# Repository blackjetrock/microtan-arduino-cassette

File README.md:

# microtan-arduino-cassette
Arduino based cassette system for Microtan computer

Uses Arduino Mega or Uno, depending on how much memory you need. Uno has 2K RAM mega has 8K. You can't use all of it for a buffer to store cassette information.

The connections to the cassette interface are not the external ones that attach to a tape recorder. They are instead pins 11 and 12 of connector B1 on the TANEX. This is logic level and removes the need for amplifiers and so on. Ground is also needed on B1.

The code runs only in fast mode. The data read from the Microtan is dumped to a buffer that can then go to an SD card.

SD card read isn't working yet.

When using the SAVE command the code displays data as it is received. The serial port on the Arduino runs at 115200 and there's enough time to send the bytes out of the port as the data is received.

Commands

clear:    Clears the memory buffer ready for a new SAVE.

display:  Displays the current contents of the buffer

savefile: Saves the buffer to a file on the attached SD card. The filename used is the embedded name in the data. 
          Data is curently saved in ASCII hex but binary is probably better as it can be directly sent back to the Microtan.

send:     Sends the data buffer back to the Microtan. There's a spurious byte at the start of the buffer that isn't sent back.

There are other commands used in development, I need to remove those or at least tidy them up.

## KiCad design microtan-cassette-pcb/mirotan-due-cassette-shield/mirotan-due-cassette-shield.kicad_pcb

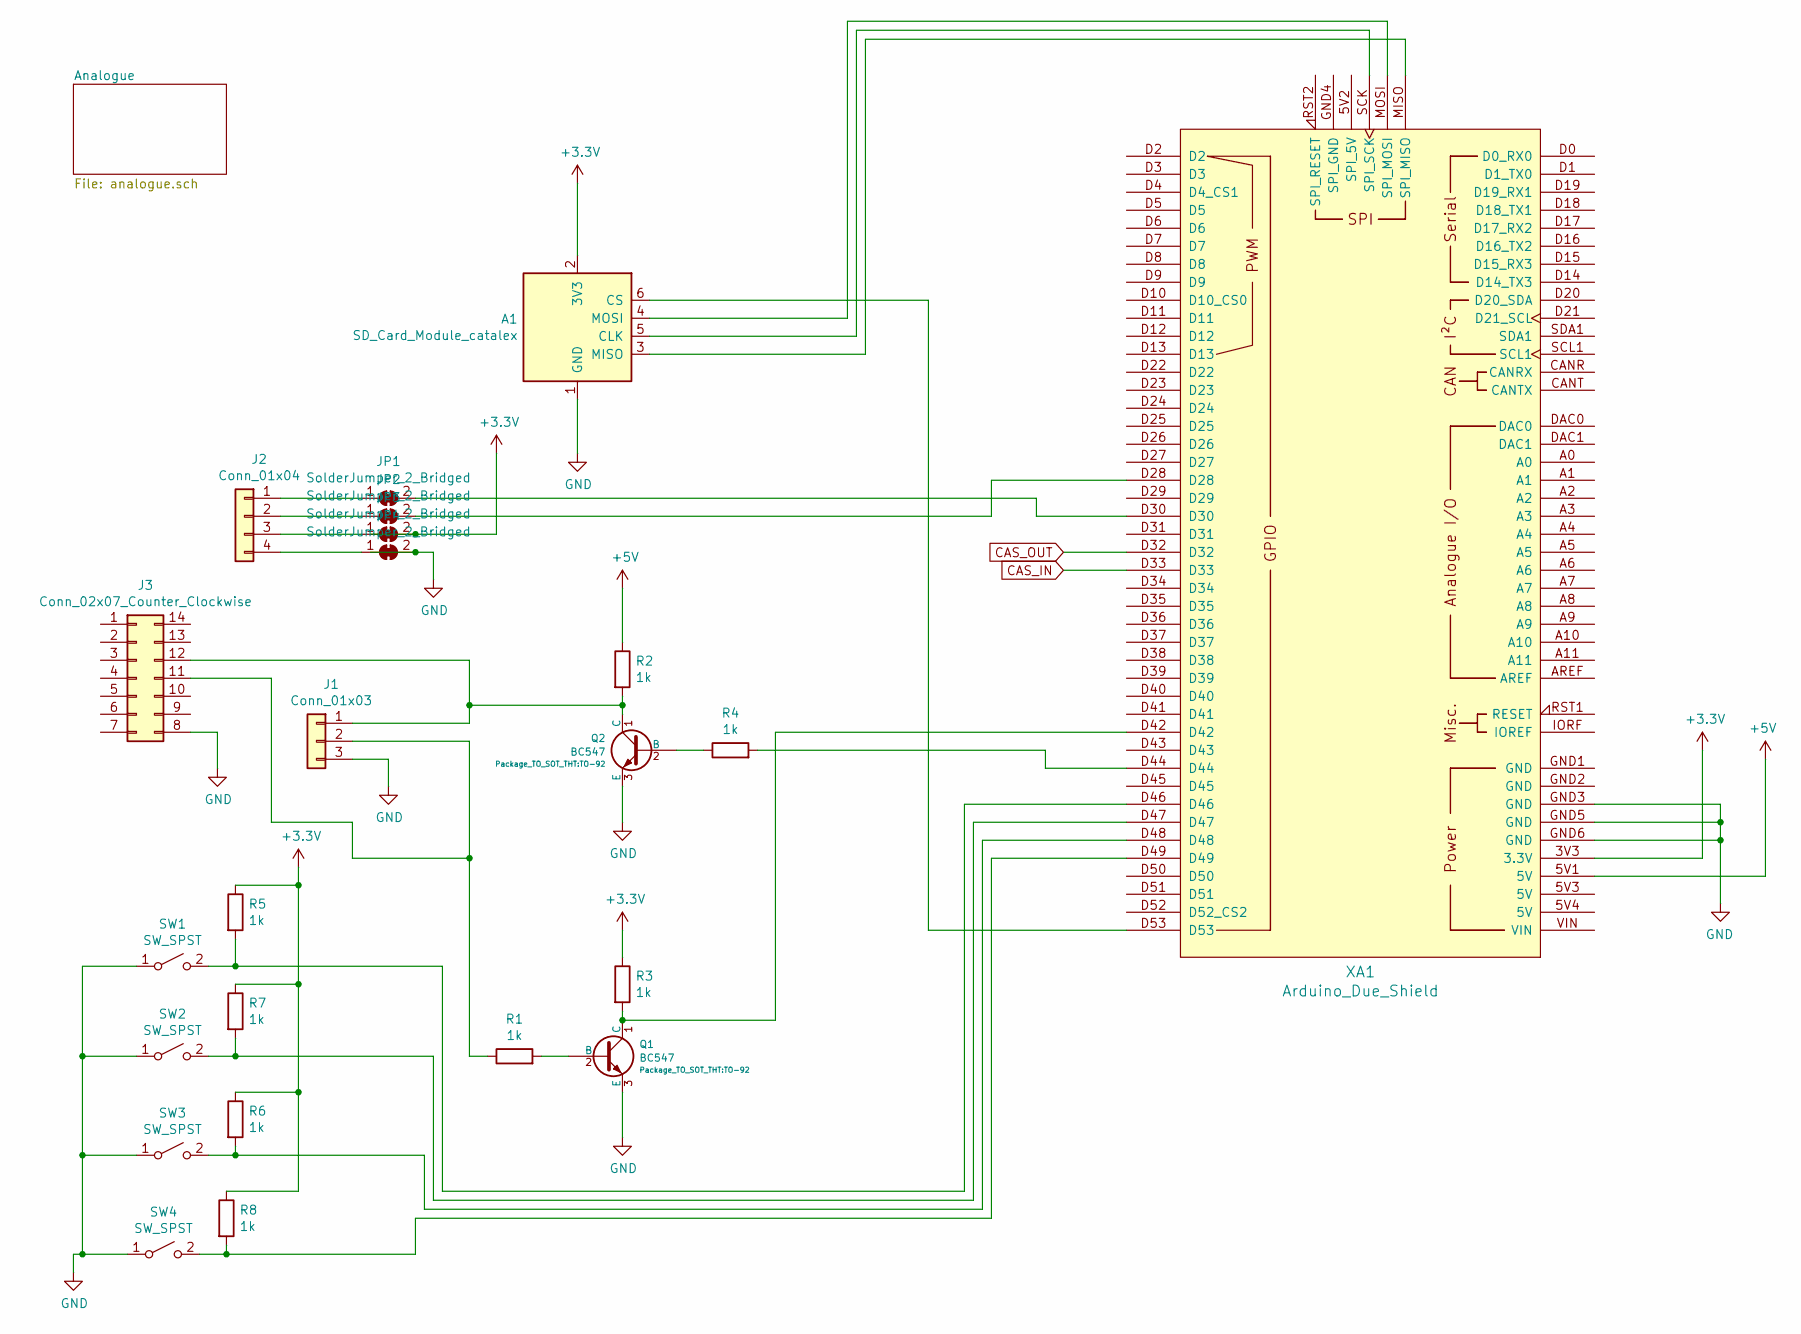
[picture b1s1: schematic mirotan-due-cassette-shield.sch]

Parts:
A1: SD_Card_Module_catalex; SD_Card_Module
J1: Conn_01x03; Molex_KK-254_AE-6410-03A_1x03_P2.54mm_Vertical
J2: Conn_01x04; Molex_KK-254_AE-6410-04A_1x04_P2.54mm_Vertical
J3: Conn_02x07_Counter_Clockwise; DIP-14_W7.62mm_Socket
JP1, JP2, JP3, JP4: SolderJumper_2_Bridged; SolderJumper-2_P1.3mm_Bridged2Bar_RoundedPad1.0x1.5mm
Q1, Q2: BC547; TO-92
R1, R2, R3, R4, R5, R6, R7, R8: 1k; R_Axial_DIN0207_L6.3mm_D2.5mm_P7.62mm_Horizontal
SW1, SW2, SW3, SW4: SW_SPST; SW_PUSH-12mm
XA1: Arduino_Due_Shield

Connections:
+3V3: A1.2 (3V3), JP3.2 (B), R3.1, R5.1, R6.1, R7.1, R8.1, XA1.3V3 (3.3V)
+5V: R2.1, XA1.5V1 (5V); also elsewhere on the board
CAS_IN: XA1.D33; also elsewhere on the board
CAS_OUT: XA1.D32; also elsewhere on the board
GND: A1.1 (GND), J1.3, J3.8, JP4.2 (B), Q1.3 (E), Q2.3 (E), SW1.1 (A), SW2.1 (A), SW3.1 (A), SW4.1 (A), XA1.GND3 (GND), XA1.GND5 (GND), XA1.GND6 (GND); also elsewhere on the board
unnamed: A1.3 (MISO), XA1.MISO (SPI_MISO)
unnamed: A1.4 (MOSI), XA1.MOSI (SPI_MOSI)
unnamed: A1.5 (CLK), XA1.SCK (SPI_SCK)
unnamed: A1.6 (CS), XA1.D53
unnamed: J1.1, J3.12, Q2.1 (C), R2.2
unnamed: J1.2, J3.11, R1.1
unnamed: J2.1, JP1.1 (A)
unnamed: J2.2, JP2.1 (A)
unnamed: J2.3, JP3.1 (A)
unnamed: J2.4, JP4.1 (A)
unnamed: JP1.2 (B), XA1.D30
unnamed: JP2.2 (B), XA1.D28
unnamed: Q1.1 (C), R3.2, XA1.D42
unnamed: Q1.2 (B), R1.2
unnamed: Q2.2 (B), R4.1
unnamed: R4.2, XA1.D44
unnamed: R5.2, SW1.2 (B), XA1.D46
unnamed: R6.2, SW3.2 (B), XA1.D48
unnamed: R7.2, SW2.2 (B), XA1.D47
unnamed: R8.2, SW4.2 (B), XA1.D49

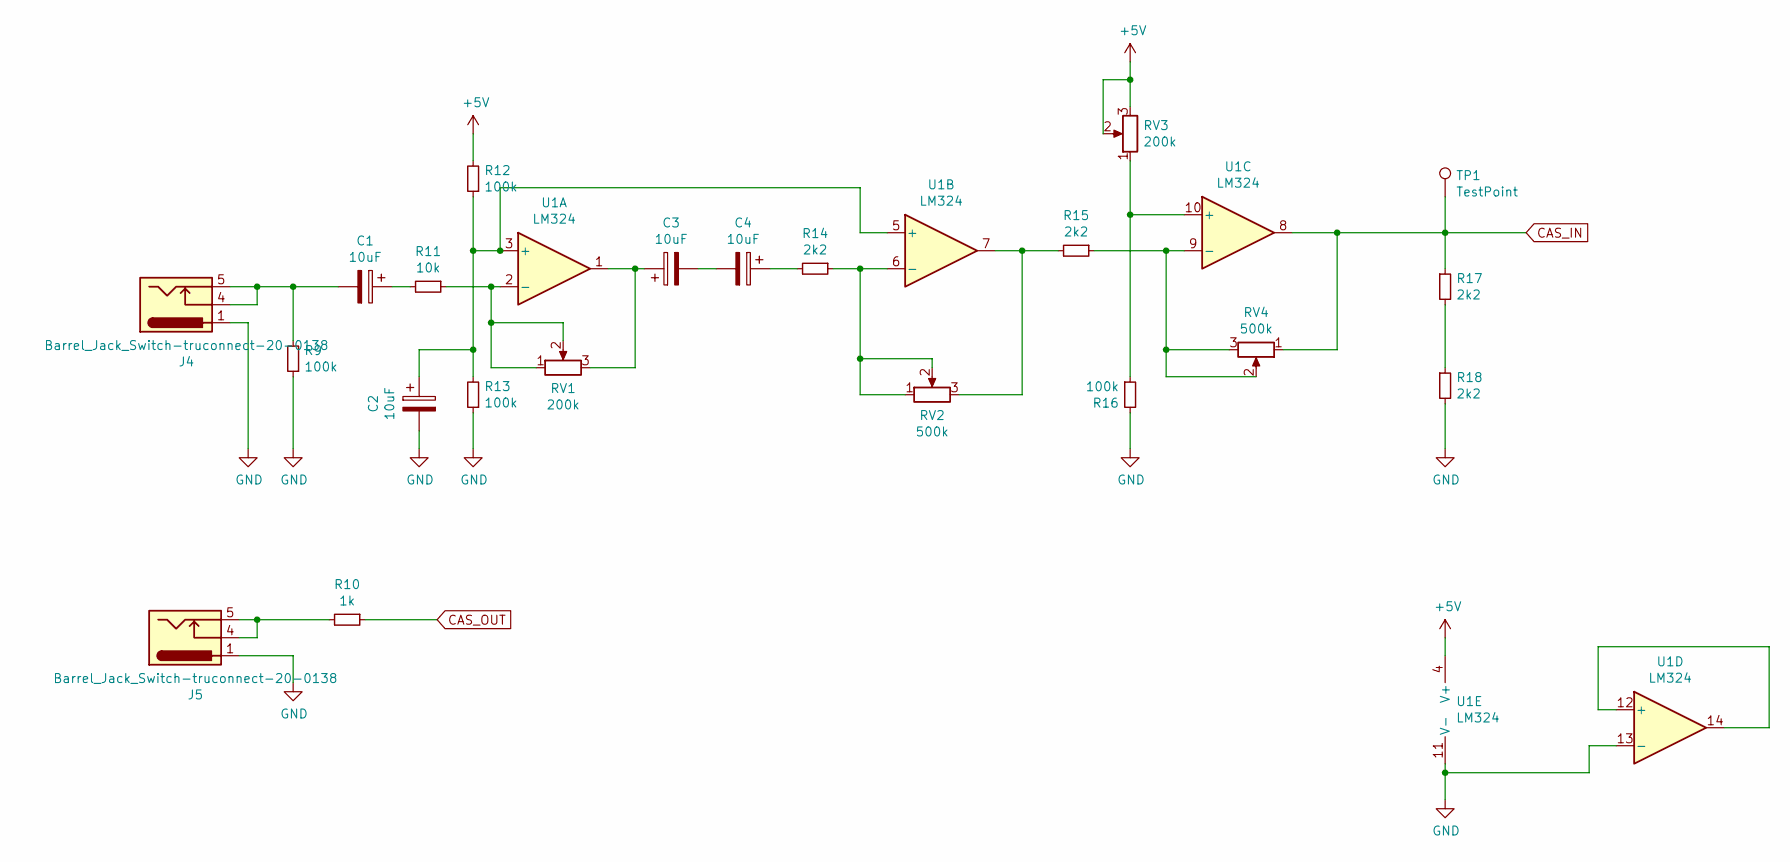
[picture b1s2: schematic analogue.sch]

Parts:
C1, C2, C3, C4: 10uF; CP_Radial_D5.0mm_P2.50mm
J4, J5: Barrel_Jack_Switch-truconnect-20-0138; truconnect-20-0138-mono-socket
R9, R12, R13, R16: 100k; R_Axial_DIN0207_L6.3mm_D2.5mm_P7.62mm_Horizontal
R10: 1k; R_Axial_DIN0207_L6.3mm_D2.5mm_P7.62mm_Horizontal
R11: 10k; R_Axial_DIN0207_L6.3mm_D2.5mm_P7.62mm_Horizontal
R14, R15, R17, R18: 2k2; R_Axial_DIN0207_L6.3mm_D2.5mm_P7.62mm_Horizontal
RV1, RV3: 200k; Potentiometer_Bourns_3296W_Vertical
RV2, RV4: 500k; Potentiometer_Bourns_3296W_Vertical
TP1: TestPoint; TestPoint_Loop_D1.80mm_Drill1.0mm_Beaded
U1: LM324; DIP-14_W7.62mm

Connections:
+5V: R12.2, RV3.2, RV3.3, U1.4 (V+); also elsewhere on the board
CAS_IN: R17.1, RV4.1, TP1.1, U1.8; also elsewhere on the board
CAS_OUT: R10.1; also elsewhere on the board
GND: C2.2, J4.1, J5.1, R9.1, R13.1, R16.2, R18.2, U1.11 (V-), U1.13 (-); also elsewhere on the board
unnamed: C1.1, R11.2
unnamed: C1.2, J4.4, J4.5, R9.2
unnamed: C2.1, R12.1, R13.2, U1.3 (+), U1.5 (+)
unnamed: C3.1, RV1.3, U1.1
unnamed: C3.2, C4.2
unnamed: C4.1, R14.2
unnamed: J5.4, J5.5, R10.2
unnamed: R11.1, RV1.1, RV1.2, U1.2 (-)
unnamed: R14.1, RV2.1, RV2.2, U1.6 (-)
unnamed: R15.1, RV4.2, RV4.3, U1.9 (-)
unnamed: R15.2, RV2.3, U1.7
unnamed: R16.1, RV3.1, U1.10 (+)
unnamed: R17.2, R18.1
unnamed: U1.12 (+), U1.14

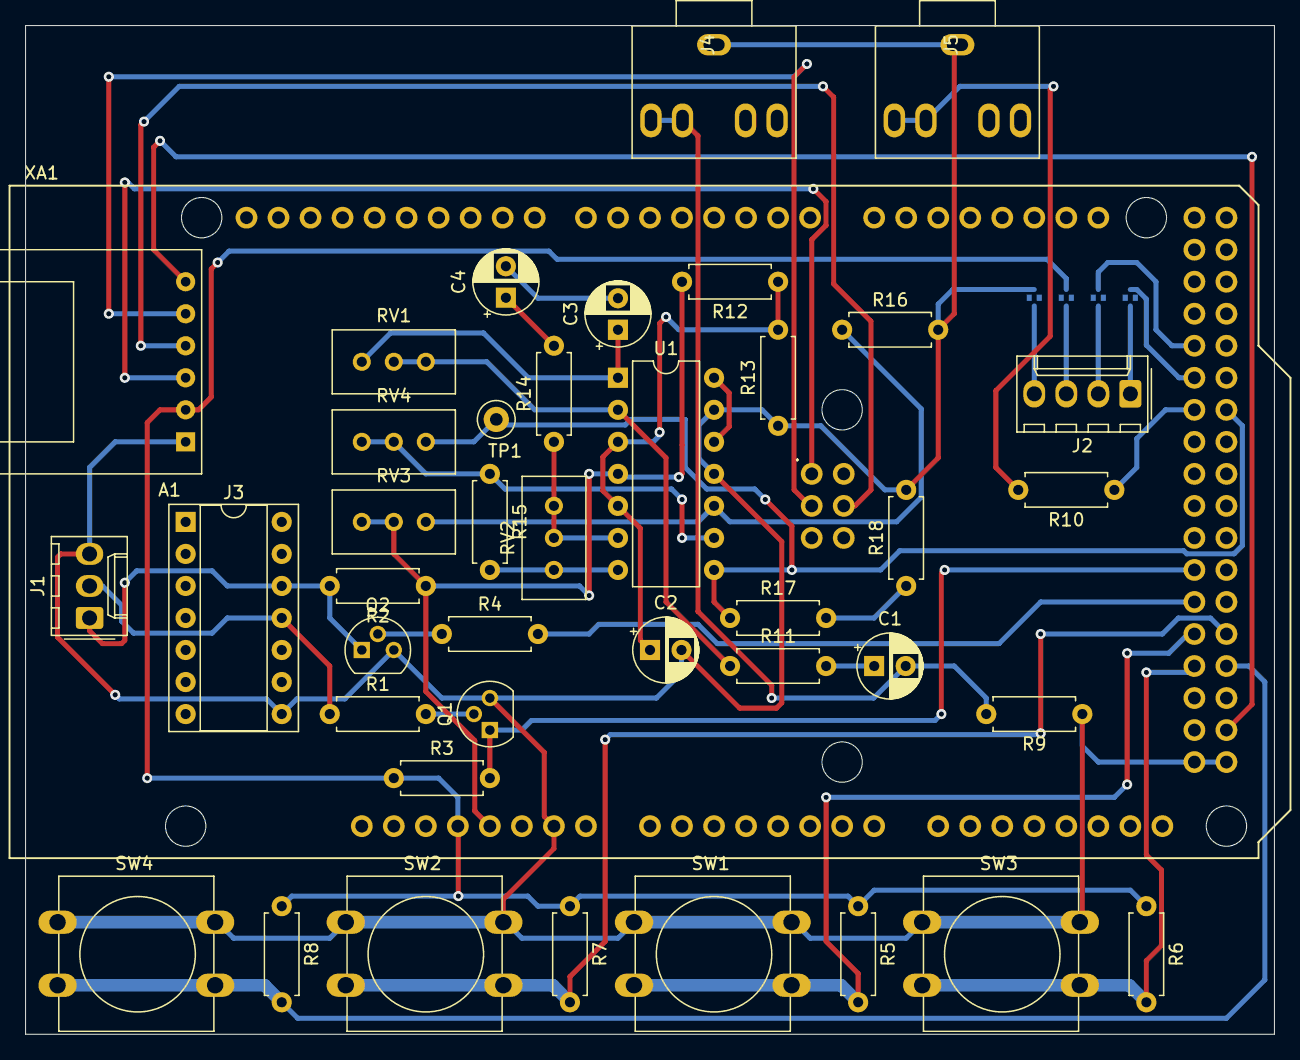
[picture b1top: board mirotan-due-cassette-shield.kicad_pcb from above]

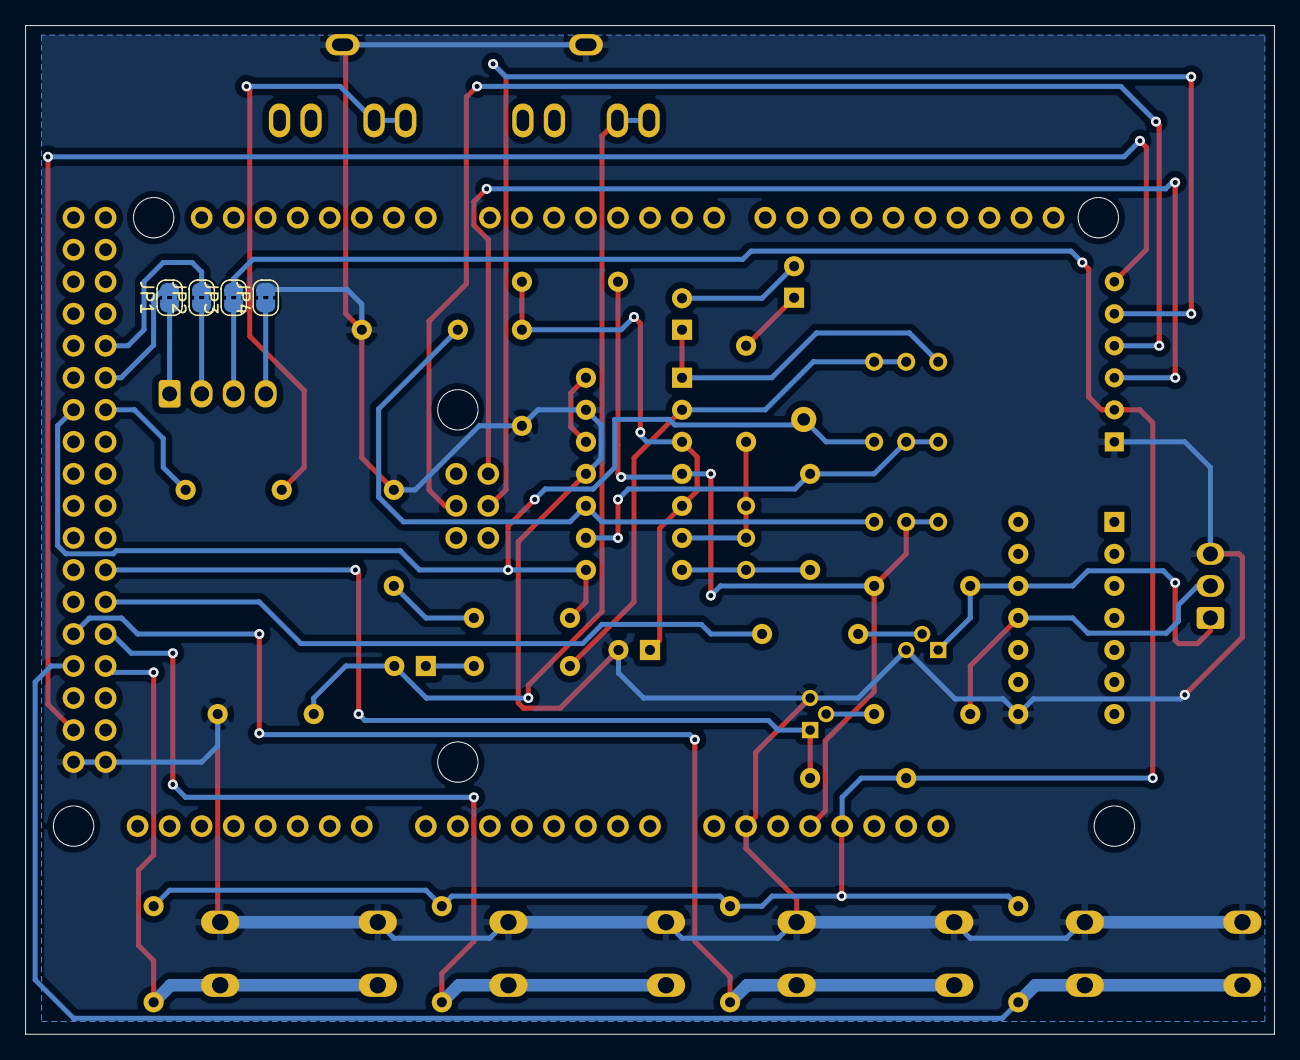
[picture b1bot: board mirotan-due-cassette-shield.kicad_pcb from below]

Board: 2 copper layers, 99.1 x 80.0 mm, 45 parts (4 on the bottom side), 39 nets.

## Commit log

2020-06-15 Initial files
2020-06-16 Version that can capture (with an extra byte at the start). loading does sort of work. There's a lot of checksum erros and memory erros, but a BASIC program can load, except for the first line. Not s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
2020-06-17 First version that can capture and send successfully. Needed 60ms burst of 0 bits after header.
2020-06-17 Added write of data to SD card file
2020-06-17 Added some SD card commands
2020-06-18 Added more file handling ommands. Read file added. Fixed listfiles problem.
2020-06-18 Added remove file command. Shortened commands for quicker entry.
2020-06-18 Fixed bug on receive.
2020-06-18 Fixed problem with delay after header
2020-06-21 Added PCB for mega on bus and cassette Updates to sketch
2020-06-23 Added changes to cassette and sketh
2020-06-24 Added Due version with switches and OLED display
2020-06-26 Updated shematic to fix problems found on PCB. Code has more OLED stuff.
2020-06-26 More sketch updates.
2020-06-27 Added Oled stuff.
2020-06-30 Menu works a lot better now
2020-07-01 menu tidy up.
2020-07-03 First fab files.
2020-07-14 Sketch updates
